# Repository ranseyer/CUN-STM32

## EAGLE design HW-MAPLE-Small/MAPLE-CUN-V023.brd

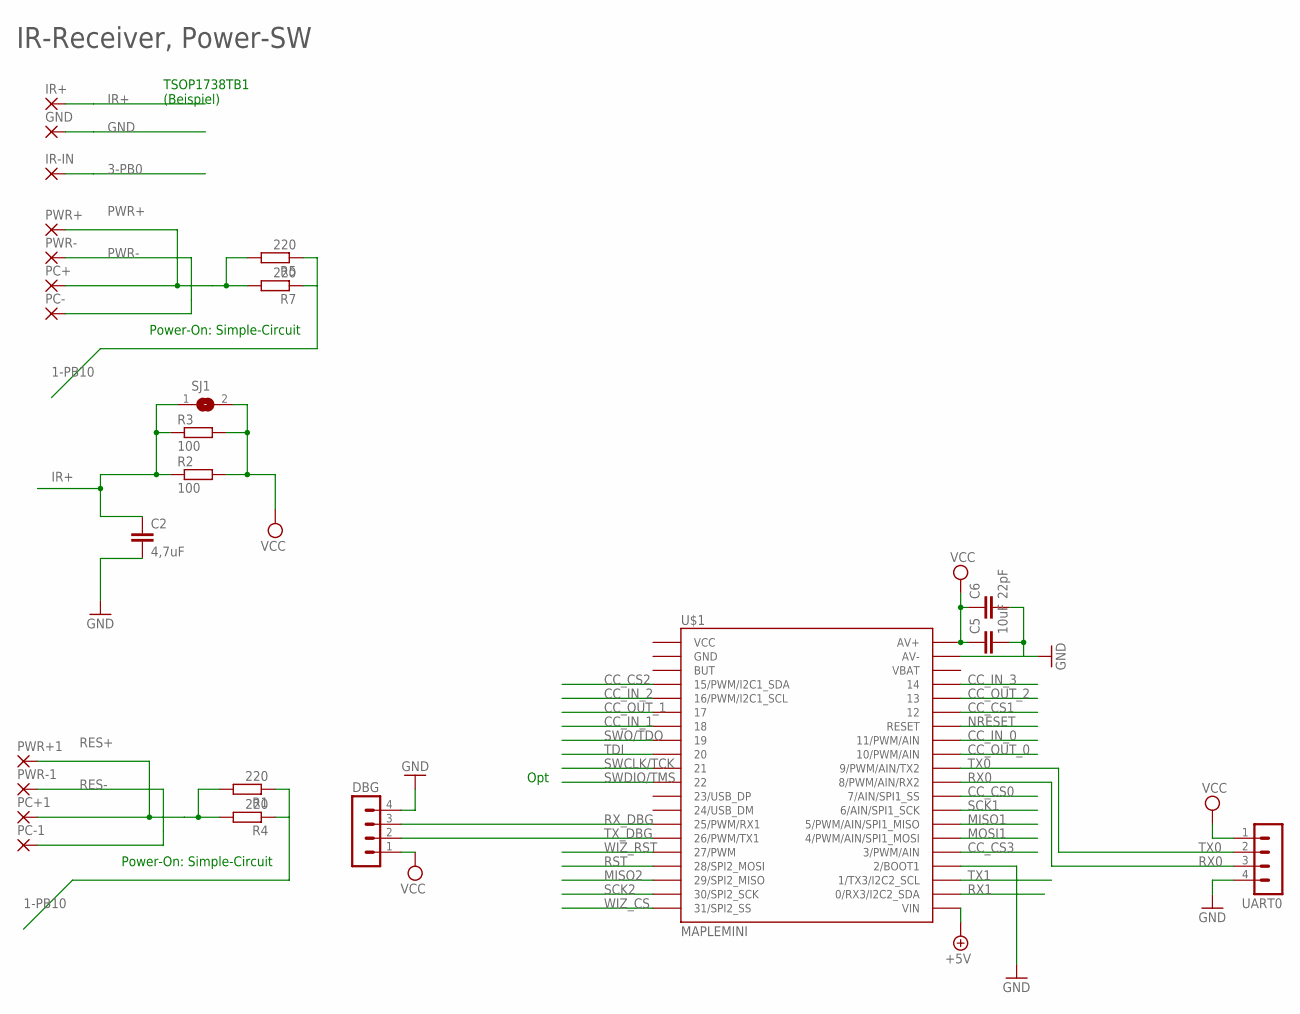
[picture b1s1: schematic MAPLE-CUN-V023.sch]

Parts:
C2: 4,7uF; C1206K
C5: 10uF; C1210
C6: 22pF; C0805
DBG: MA04-1
GND: SMD2; SMD1,27-2,54
IR+: SMD2; SMD1,27-2,54
IR-IN: SMD2; SMD1,27-2,54
PC+, PC+1: SMD2; SMD1,27-2,54
PC-, PC-1: SMD2; SMD1,27-2,54
PWR+, PWR+1: SMD2; SMD1,27-2,54
PWR-, PWR-1: SMD2; SMD1,27-2,54
R1, R5: 220; 0204/7
R2: 100; 0204/7
R3: 100; R0805W
R4, R7: 220; R0805W
SJ1: SJ
U$1: MAPLEMINI; 20-DIP
UART0: MA04-1

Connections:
1-PB10: R1.1, R4.1, R5.1, R7.1
3-PB0: IR-IN.1
+5V: U$1.21 (VIN)
CC_CS0: U$1.29 (7/AIN/SPI1_SS)
CC_CS1: U$1.35 (12)
CC_CS2: U$1.4 (15/PWM/I2C1_SDA)
CC_CS3: U$1.25 (3/PWM/AIN)
CC_IN_0: U$1.33 (11/PWM/AIN)
CC_IN_1: U$1.7 (18)
CC_IN_2: U$1.5 (16/PWM/I2C1_SCL)
CC_IN_3: U$1.37 (14)
CC_OUT_0: U$1.32 (10/PWM/AIN)
CC_OUT_1: U$1.6 (17)
CC_OUT_2: U$1.36 (13)
GND: C2.2, C5.2, C6.2, DBG.4, GND.1, U$1.24 (2/BOOT1), U$1.39 (AV-), UART0.4
IR+: C2.1, IR+.1, R2.1, R3.1, SJ1.1
MISO1: U$1.27 (5/PWM/AIN/SPI1_MISO)
MISO2: U$1.18 (29/SPI2_MISO)
MOSI1: U$1.26 (4/PWM/AIN/SPI1_MOSI)
NRESET: U$1.34 (RESET)
PWR+: PC+.1, PWR+.1, R5.2, R7.2
PWR-: PC-.1, PWR-.1
RES+: PC+1.1, PWR+1.1, R1.2, R4.2
RES-: PC-1.1, PWR-1.1
RST: U$1.17 (28/SPI2_MOSI)
RX0: U$1.30 (8/PWM/AIN/RX2), UART0.3
RX1: U$1.22 (0/RX3/I2C2_SDA)
RX_DBG: DBG.3, U$1.14 (25/PWM/RX1)
SCK1: U$1.28 (6/AIN/SPI1_SCK)
SCK2: U$1.19 (30/SPI2_SCK)
SWCLK/TCK: U$1.10 (21)
SWDIO/TMS: U$1.11 (22)
SWO/TDO: U$1.8 (19)
TDI: U$1.9 (20)
TX0: U$1.31 (9/PWM/AIN/TX2), UART0.2
TX1: U$1.23 (1/TX3/I2C2_SCL)
TX_DBG: DBG.2, U$1.15 (26/PWM/TX1)
VCC: C5.1, C6.1, DBG.1, R2.2, R3.2, SJ1.2, U$1.40 (AV+), UART0.1
WIZ_CS: U$1.20 (31/SPI2_SS)
WIZ_RST: U$1.16 (27/PWM)

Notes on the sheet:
Opt
TSOP1738TB1 (Beispiel)
Power-On: Simple-Circuit
IR-Receiver, Power-SW

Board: 2 copper layers, 24 parts (0 on the bottom side), 12 nets, no tracks yet.

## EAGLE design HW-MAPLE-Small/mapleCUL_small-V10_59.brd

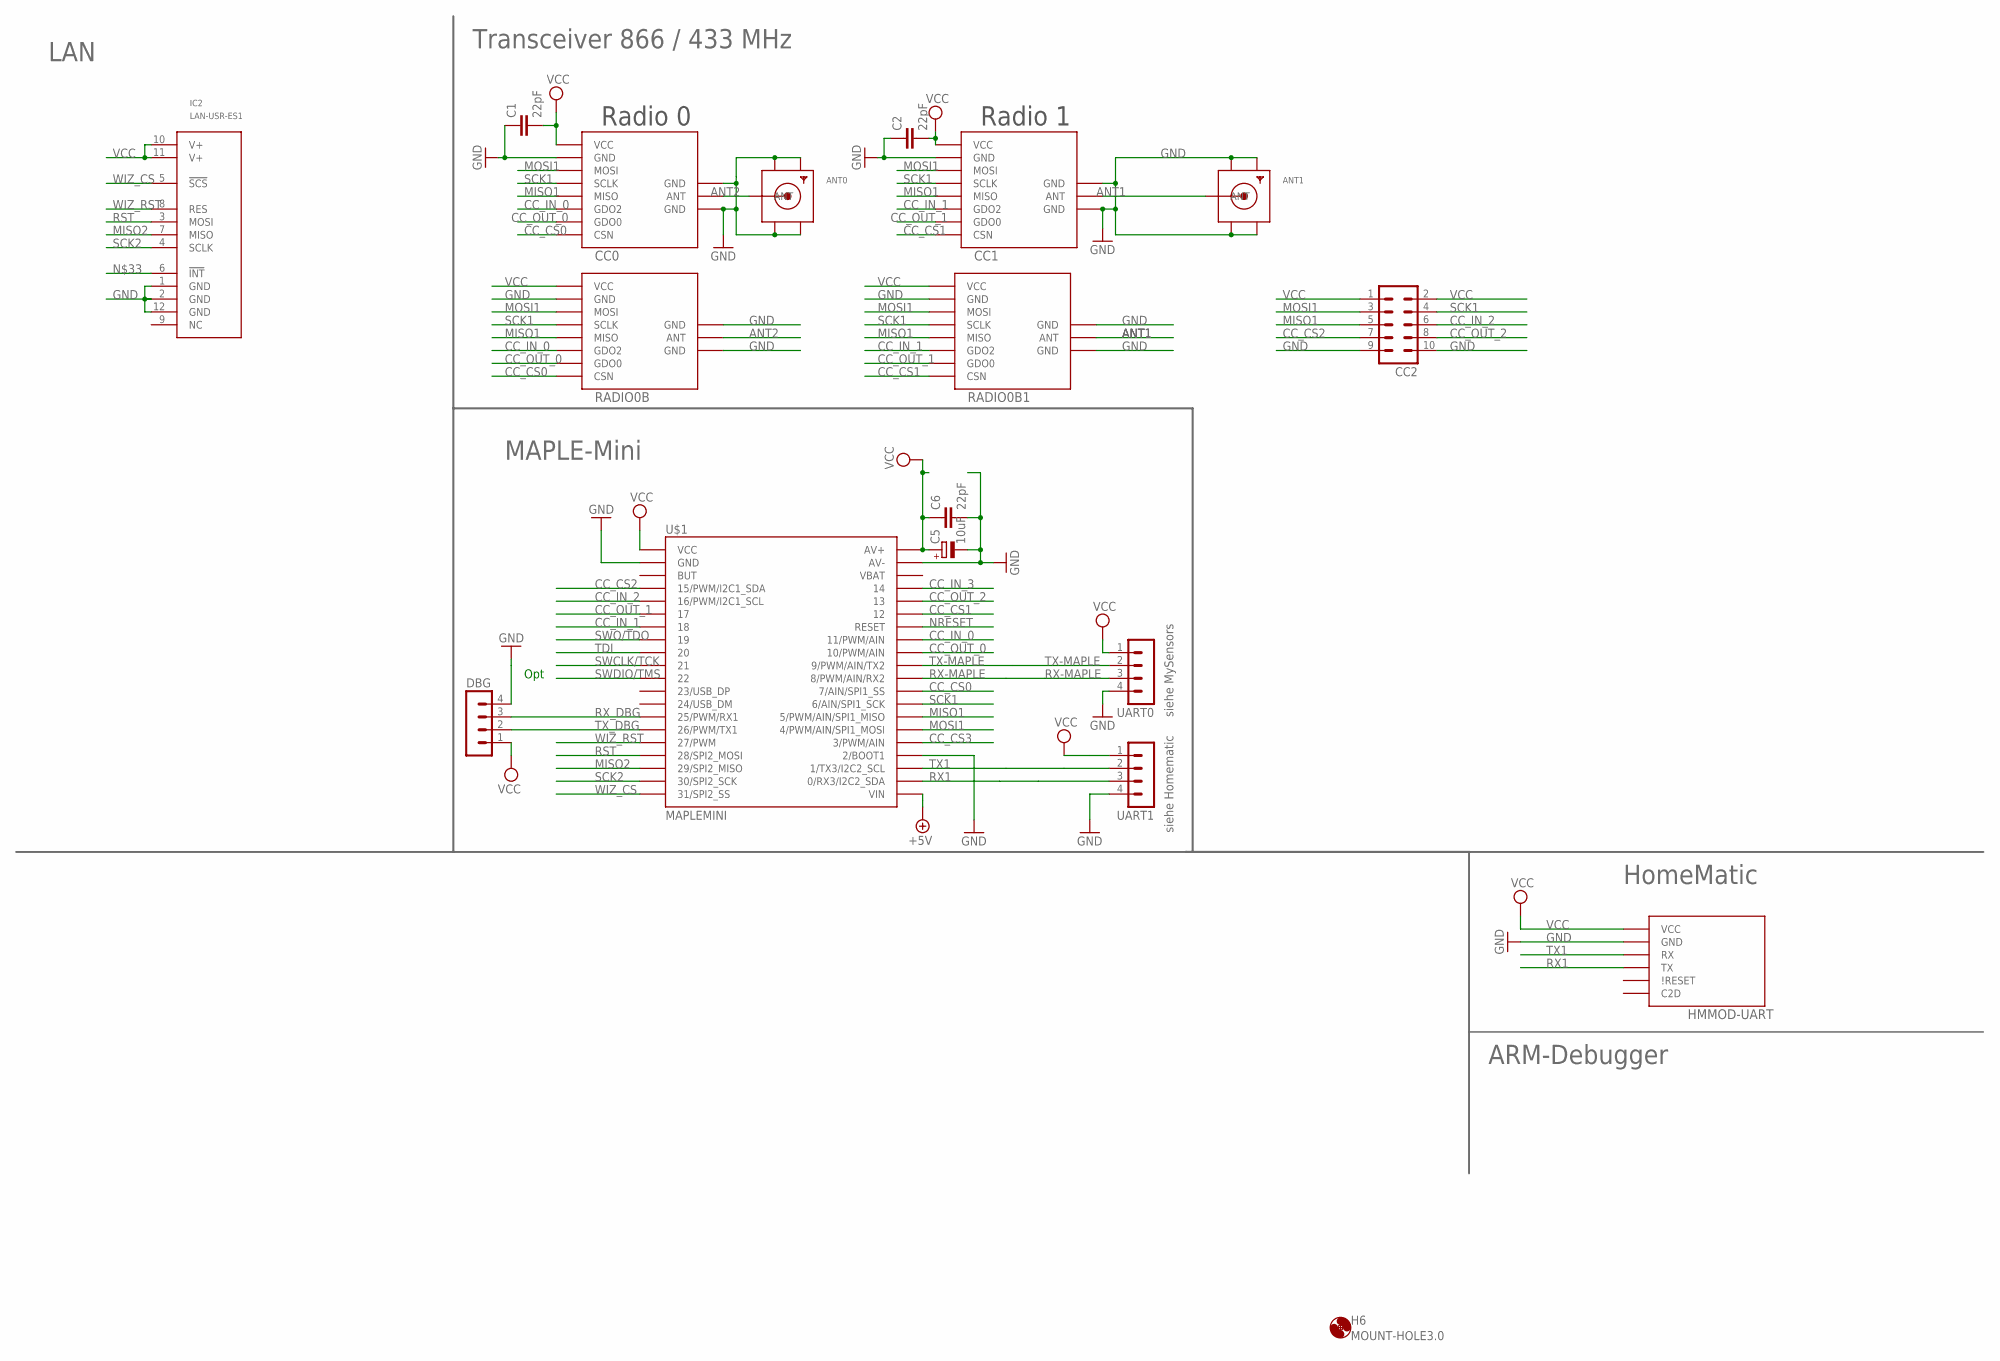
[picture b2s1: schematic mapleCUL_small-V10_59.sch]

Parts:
ANT0, ANT1: SMACONNECTOR_EDGE_UFL; SMA_EDGELAUNCH_UFL
C1, C2, C6: 22pF; C0805
C5: 10uF; R/2012-12W
CC0: CC1101; CC1101_MODULE1_SMD
CC1: CC1101_MODULE1SMD; CC1101_MODULE1_SMD
CC2: MA05-2
DBG: MA04-1
H6: MOUNT-HOLE3.0; 3,0
HMMOD-UART: HM-MOD-UARTDIL; HM-MOD-UART-DIL
IC2: LAN-USR-ES1; USR-ES1
RADIO0B: CC1101_MODULE1SMALL; CC1101_MODULE1_SMD
RADIO0B1: CC1101_MODULE1SMD; CC1101_MODULE1_SMD
U$1: MAPLEMINI; 20-DIP
UART0, UART1: MA04-1

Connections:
+5V: U$1.21 (VIN)
ANT1: ANT1.P (ANT), CC1.ANT, RADIO0B1.ANT
ANT2: ANT0.P (ANT), CC0.ANT, RADIO0B.ANT
CC_CS0: CC0.CSN, RADIO0B.CSN, U$1.29 (7/AIN/SPI1_SS)
CC_CS1: CC1.CSN, RADIO0B1.CSN, U$1.35 (12)
CC_CS2: CC2.7, U$1.4 (15/PWM/I2C1_SDA)
CC_CS3: U$1.25 (3/PWM/AIN)
CC_IN_0: CC0.GDO2, RADIO0B.GDO2, U$1.33 (11/PWM/AIN)
CC_IN_1: CC1.GDO2, RADIO0B1.GDO2, U$1.7 (18)
CC_IN_2: CC2.6, U$1.5 (16/PWM/I2C1_SCL)
CC_IN_3: U$1.37 (14)
CC_OUT_0: CC0.GDO0, RADIO0B.GDO0, U$1.32 (10/PWM/AIN)
CC_OUT_1: CC1.GDO0, RADIO0B1.GDO0, U$1.6 (17)
CC_OUT_2: CC2.8, U$1.36 (13)
GND: ANT0.GND@1 (GND1), ANT0.GND@2 (GND2), ANT0.GND@3 (GND3), ANT0.GND@4 (GND4), ANT1.GND@1 (GND1), ANT1.GND@2 (GND2), ANT1.GND@3 (GND3), ANT1.GND@4 (GND4), C1.1, C2.1, C5.-, C6.2, CC0.GND@0 (GND), CC0.GND@1 (GND), CC0.GND@2 (GND), CC1.GND@0 (GND), CC1.GND@1 (GND), CC1.GND@2 (GND), CC2.9, CC2.10, DBG.4, HMMOD-UART.2 (GND), IC2.1 (GND), IC2.2 (GND), IC2.12 (GND), RADIO0B.GND@0 (GND), RADIO0B.GND@1 (GND), RADIO0B.GND@2 (GND), RADIO0B1.GND@0 (GND), RADIO0B1.GND@1 (GND), RADIO0B1.GND@2 (GND), U$1.2 (GND), U$1.24 (2/BOOT1), U$1.39 (AV-), UART0.4, UART1.4
MISO1: CC0.MISO, CC1.MISO, CC2.5, RADIO0B.MISO, RADIO0B1.MISO, U$1.27 (5/PWM/AIN/SPI1_MISO)
MISO2: IC2.7 (MISO), U$1.18 (29/SPI2_MISO)
MOSI1: CC0.MOSI, CC1.MOSI, CC2.3, RADIO0B.MOSI, RADIO0B1.MOSI, U$1.26 (4/PWM/AIN/SPI1_MOSI)
NRESET: U$1.34 (RESET)
RST: IC2.3 (MOSI), U$1.17 (28/SPI2_MOSI)
RX1: HMMOD-UART.5 (TX), U$1.22 (0/RX3/I2C2_SDA), UART1.3
RX-MAPLE: U$1.30 (8/PWM/AIN/RX2), UART0.3
RX_DBG: DBG.3, U$1.14 (25/PWM/RX1)
SCK1: CC0.SCLK, CC1.SCLK, CC2.4, RADIO0B.SCLK, RADIO0B1.SCLK, U$1.28 (6/AIN/SPI1_SCK)
SCK2: IC2.4 (SCLK), U$1.19 (30/SPI2_SCK)
SWCLK/TCK: U$1.10 (21)
SWDIO/TMS: U$1.11 (22)
SWO/TDO: U$1.8 (19)
TDI: U$1.9 (20)
TX1: HMMOD-UART.6 (RX), U$1.23 (1/TX3/I2C2_SCL), UART1.2
TX-MAPLE: U$1.31 (9/PWM/AIN/TX2), UART0.2
TX_DBG: DBG.2, U$1.15 (26/PWM/TX1)
VCC: C1.2, C2.2, C5.+, C6.1, CC0.VCC, CC1.VCC, CC2.1, CC2.2, DBG.1, HMMOD-UART.1 (VCC), IC2.10 (V+), IC2.11 (V+), RADIO0B.VCC, RADIO0B1.VCC, U$1.1 (VCC), U$1.40 (AV+), UART0.1, UART1.1
WIZ_CS: IC2.5 (!SCS!), U$1.20 (31/SPI2_SS)
WIZ_RST: IC2.8 (RES), U$1.16 (27/PWM)

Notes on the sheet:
Radio 1
Radio 0
Opt
siehe Homematic
siehe MySensors
HomeMatic
MAPLE-Mini
Transceiver 866 / 433 MHz
LAN
ARM-Debugger

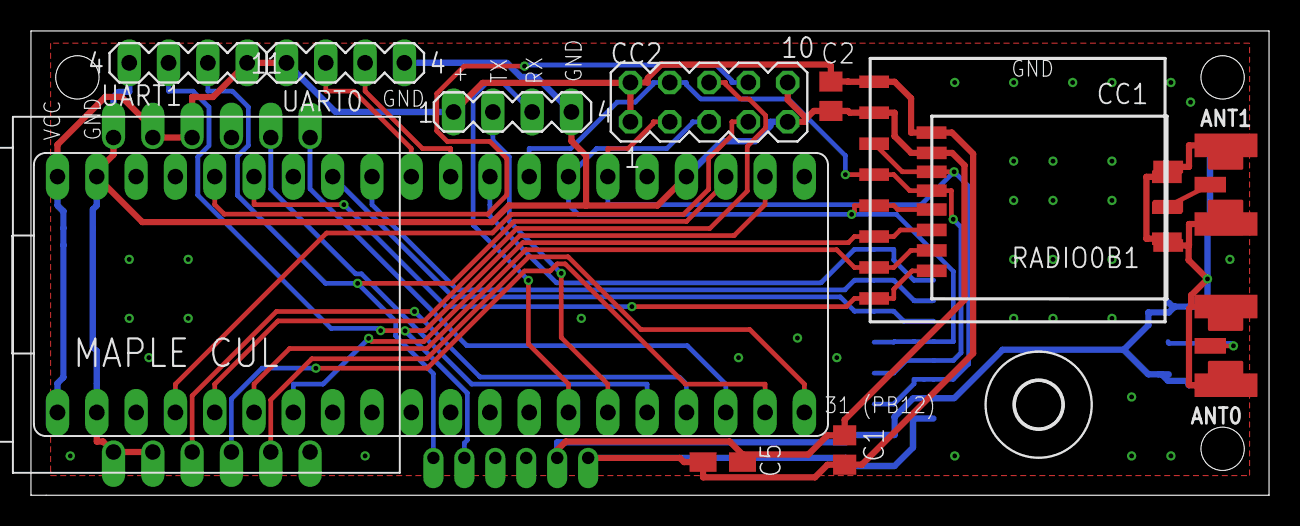
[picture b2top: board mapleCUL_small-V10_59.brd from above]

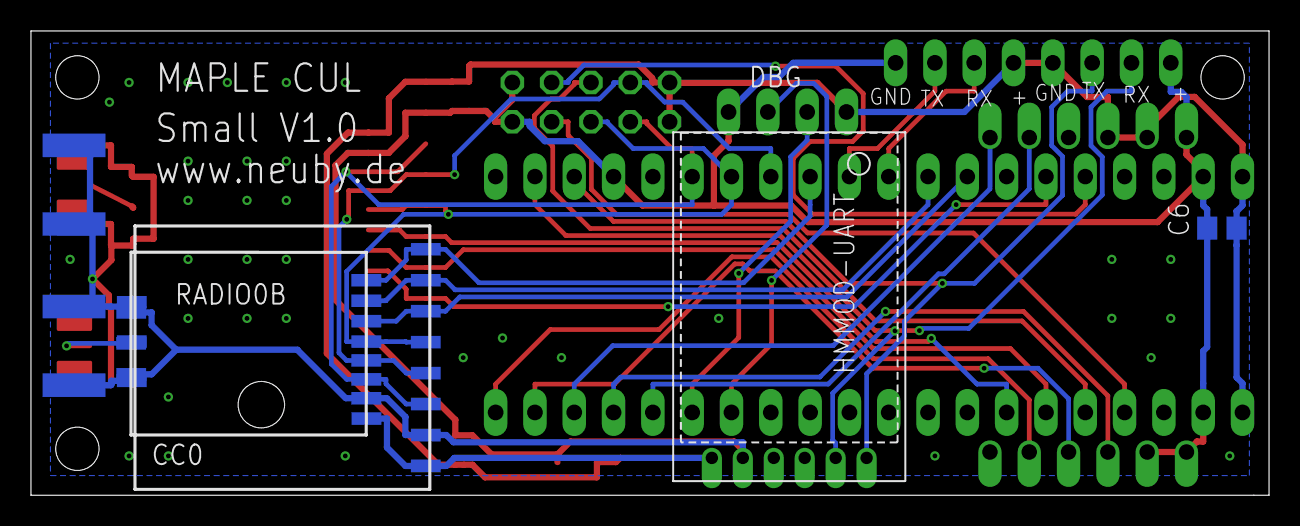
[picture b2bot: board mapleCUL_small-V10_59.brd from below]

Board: 2 copper layers, 80.0 x 30.0 mm, 18 parts (4 on the bottom side), 27 nets.

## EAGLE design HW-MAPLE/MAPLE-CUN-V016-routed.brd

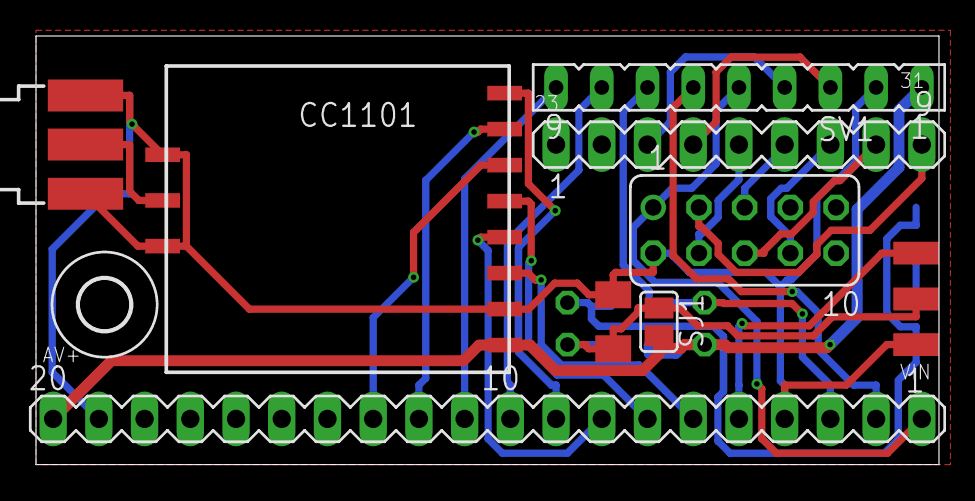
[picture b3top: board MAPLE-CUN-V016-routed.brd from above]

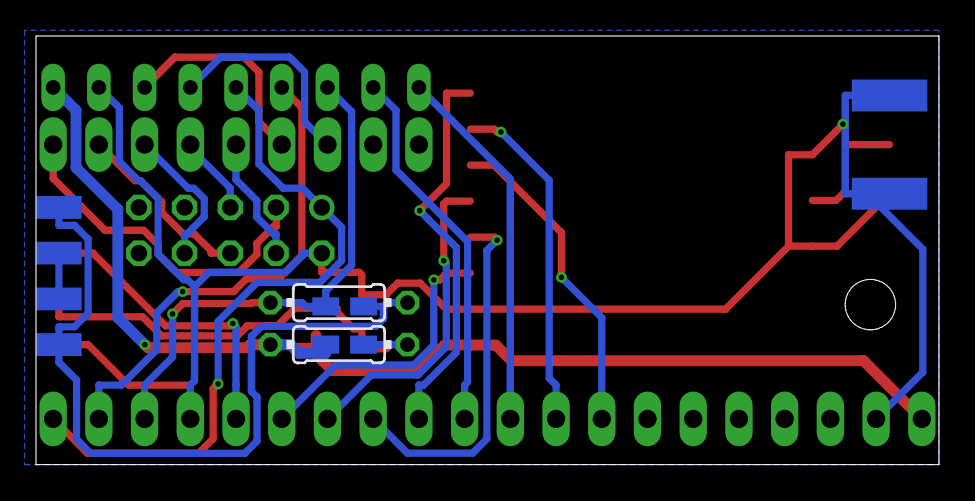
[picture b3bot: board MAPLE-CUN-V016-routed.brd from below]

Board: 2 copper layers, 50.2 x 23.8 mm, 20 parts (8 on the bottom side), 25 nets.

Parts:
C2: 4,7uF; C1206K
CC1101: CC1101_MODULE1SMD; CC1101_MODULE1_SMD
GND: SMD1,27-2,54
H1: MOUNT-HOLE2.8; 2,8
IR+: SMD1,27-2,54
IR-IN: SMD1,27-2,54
PC+: SMD1,27-2,54
PC-: SMD1,27-2,54
PWR+: SMD1,27-2,54
PWR-: SMD1,27-2,54
R2: 100; 0204/7
R3: 100; R0805W
R5: 220; 0204/7
R7: 220; R0805W
SJ1: SJ
SV1: FE09
SV4: MA20-1
SV5: MA09-1
W5100: FE05-2
X1: SMA

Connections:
0-PB11: SV1.6, SV4.2
1-PB10: R5.1, R7.1, SV1.7, SV4.3
3-PB0: IR-IN.1, SV4.5
+5V: SV1.5, SV4.1, W5100.1
CC_IN_0: CC1101.GDO2, SV4.13
CC_OUT_0: CC1101.GDO0, SV4.12
CSN: CC1101.CSN, SV4.9
GND: C2.2, CC1101.GND@0, CC1101.GND@1, CC1101.GND@2, GND.1, SV1.2, SV4.4, SV4.19, W5100.2, X1.GND@1, X1.GND@2, X1.GND@3, X1.GND@4
IR+: C2.1, IR+.1, R2.1, R3.1, SJ1.1
MISO2: SV5.7, W5100.8
MOSI: CC1101.MOSI, SV4.6
MOSI2: SV5.6, W5100.5
unnamed: CC1101.ANT, X1.1
unnamed: CC1101.MISO, SV4.7
unnamed: CC1101.SCLK, SV4.8
PWR+: PC+.1, PWR+.1, R5.2, R7.2
PWR-: PC-.1, PWR-.1
RX1: SV1.4, SV5.3
S2RX: SV1.8, SV4.10
S2TX: SV1.9, SV4.11
SCK2: SV5.8, W5100.6
TX1: SV1.3, SV5.4
VCC: CC1101.VCC, R2.2, R3.2, SJ1.2, SV1.1, SV4.20
WIZ_CS: SV5.9, W5100.3
WIZ_RST: SV5.5, W5100.4

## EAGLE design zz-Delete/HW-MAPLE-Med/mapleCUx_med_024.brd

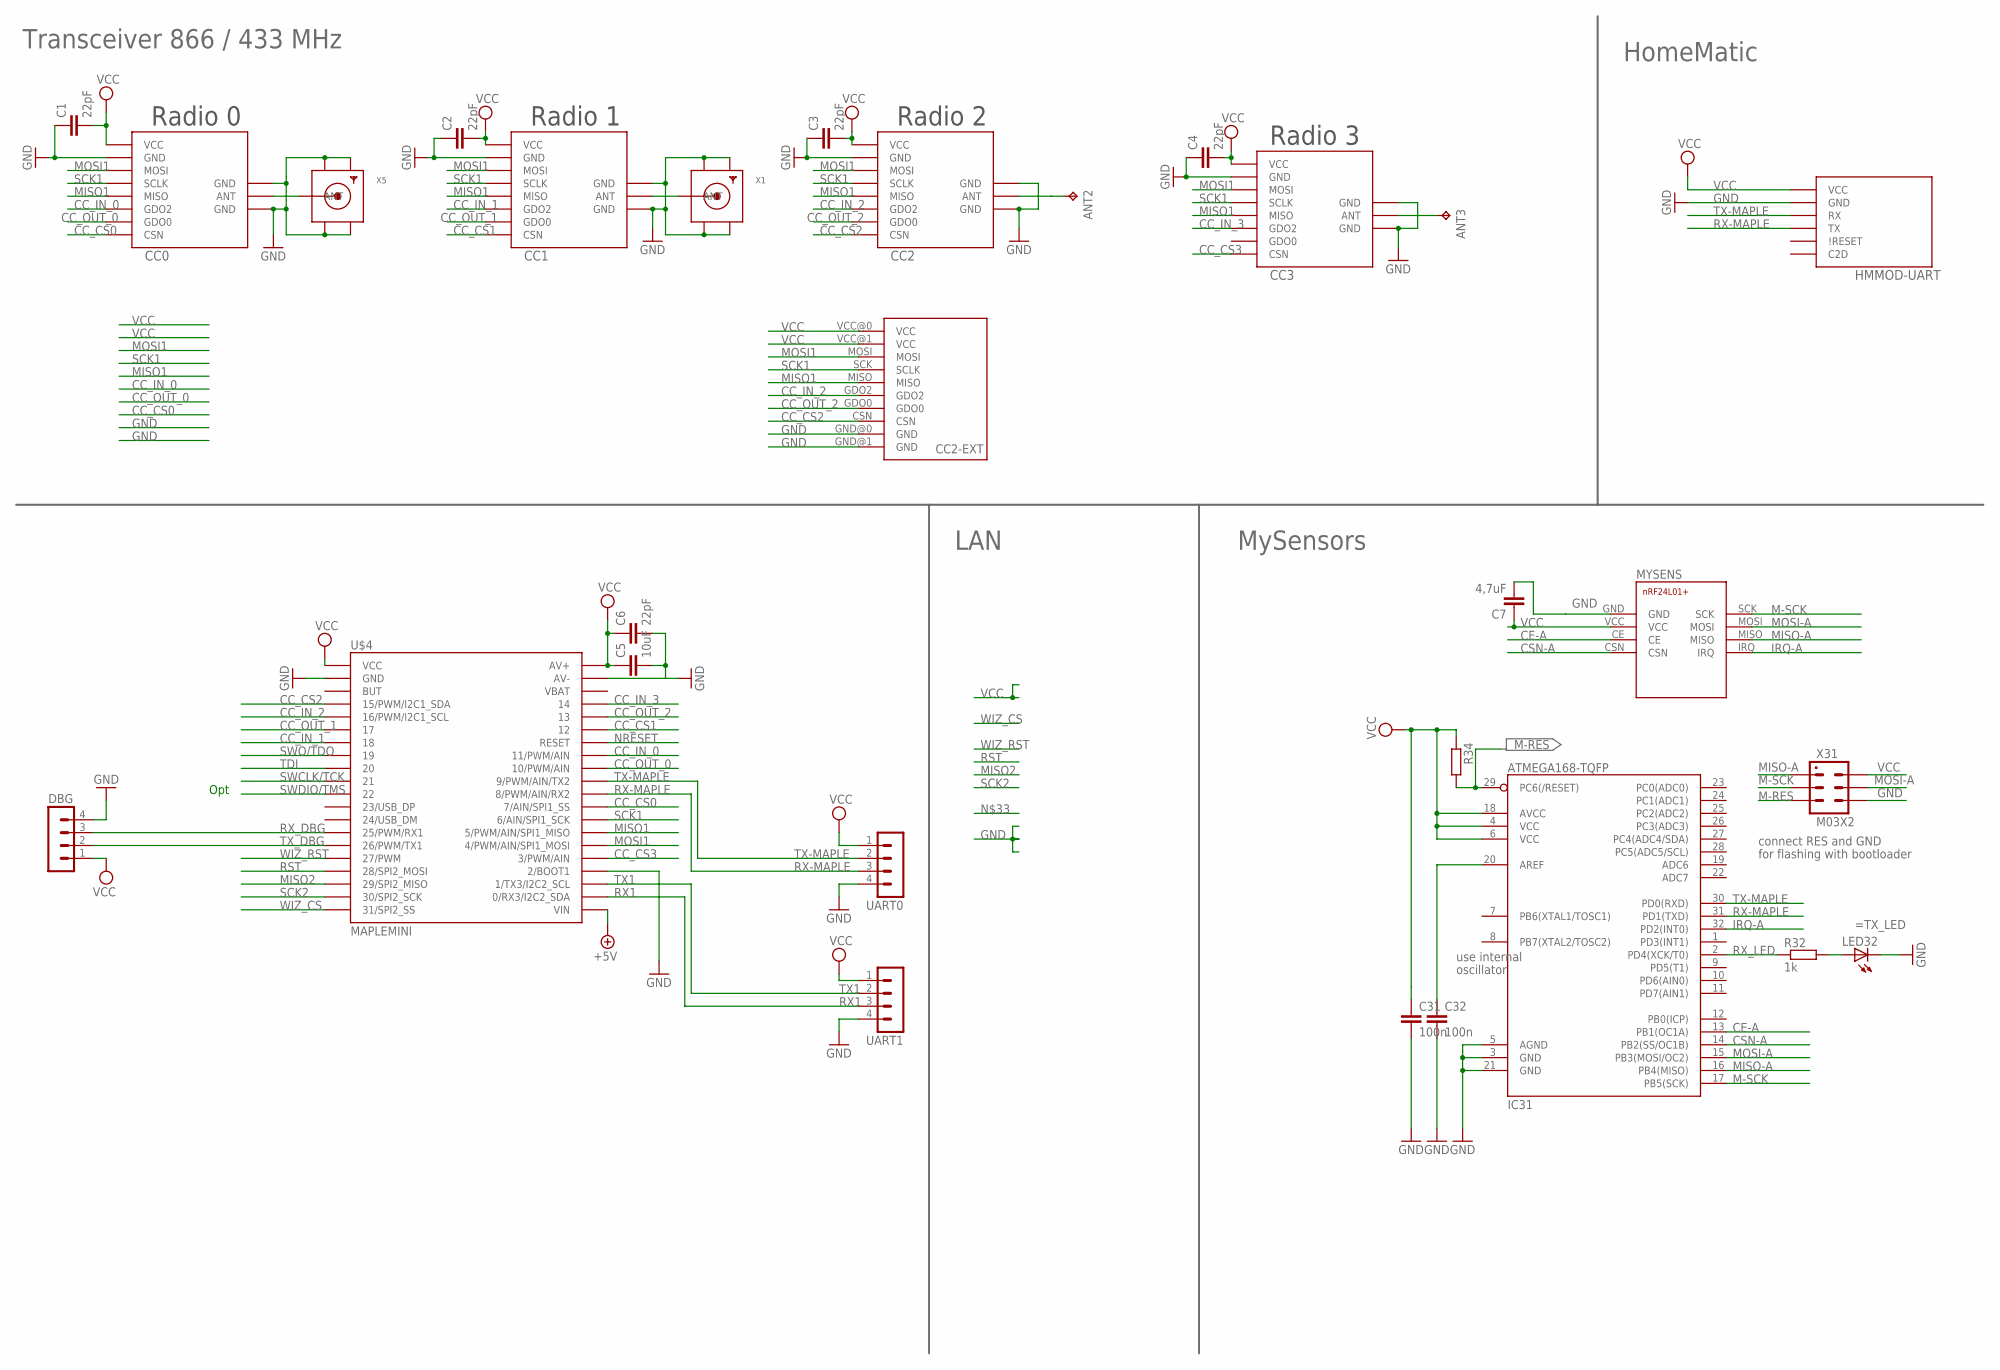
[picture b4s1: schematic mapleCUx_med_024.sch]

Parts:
ANT2, ANT3: TPPAD1-13; P1-13
C1, C2, C3, C4, C6: 22pF; C0805
C5: 10uF; C1210
C7: 4,7uF; C1210
C31, C32: 100n; C0805
CC0: CC1101; CC1101_MODULE1_SMD
CC1, CC2, CC3: CC1101_MODULE1SMD; CC1101_MODULE1_SMD
CC2-EXT: CC1101_MODULE3_DIL
DBG: MA04-1
HMMOD-UART: HM-MOD-UARTDIL; HM-MOD-UART-DIL
IC31: ATMEGA168-TQFP; TQFP32-08
LED32: LEDCHIPLED_0805; CHIPLED_0805
MYSENS: NRF24L01+SMD
R32: 1k; R0805
R34: R-EU_R0805; R0805
U$4: MAPLEMINI; 20-DIP
UART0, UART1: MA04-1
X1, X5: SMACONNECTOR_EDGE_UFL; SMA_EDGELAUNCH_UFL
X31: M03X2; 2X03-1.27MM_SMD

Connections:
+5V: U$4.21 (VIN)
CC_CS0: CC0.CSN, U$4.29 (7/AIN/SPI1_SS)
CC_CS1: CC1.CSN, U$4.35 (12)
CC_CS2: CC2.CSN, CC2-EXT.CSN, U$4.4 (15/PWM/I2C1_SDA)
CC_CS3: CC3.CSN, U$4.25 (3/PWM/AIN)
CC_IN_0: CC0.GDO2, U$4.33 (11/PWM/AIN)
CC_IN_1: CC1.GDO2, U$4.7 (18)
CC_IN_2: CC2.GDO2, CC2-EXT.GDO2, U$4.5 (16/PWM/I2C1_SCL)
CC_IN_3: CC3.GDO2, U$4.37 (14)
CC_OUT_0: CC0.GDO0, U$4.32 (10/PWM/AIN)
CC_OUT_1: CC1.GDO0, U$4.6 (17)
CC_OUT_2: CC2.GDO0, CC2-EXT.GDO0, U$4.36 (13)
CE-A: IC31.13 (PB1(OC1A)), MYSENS.CE
CSN-A: IC31.14 (PB2(SS/OC1B)), MYSENS.CSN
GND: C1.1, C2.1, C3.1, C4.1, C5.2, C6.2, C7.2, C31.2, C32.2, CC0.GND@0 (GND), CC0.GND@1 (GND), CC0.GND@2 (GND), CC1.GND@0 (GND), CC1.GND@1 (GND), CC1.GND@2 (GND), CC2.GND@0 (GND), CC2.GND@1 (GND), CC2.GND@2 (GND), CC2-EXT.GND@0 (GND), CC2-EXT.GND@1 (GND), CC3.GND@0 (GND), CC3.GND@1 (GND), CC3.GND@2 (GND), DBG.4, HMMOD-UART.2 (GND), IC31.3 (GND), IC31.5 (AGND), IC31.21 (GND), LED32.C, MYSENS.GND, U$4.2 (GND), U$4.24 (2/BOOT1), U$4.39 (AV-), UART0.4, UART1.4, X1.GND@1 (GND1), X1.GND@2 (GND2), X1.GND@3 (GND3), X1.GND@4 (GND4), X5.GND@1 (GND1), X5.GND@2 (GND2), X5.GND@3 (GND3), X5.GND@4 (GND4), X31.P$6 (6)
IRQ-A: IC31.32 (PD2(INT0)), MYSENS.IRQ
M-RES: IC31.29 (PC6(/RESET)), R34.2, X31.P$5 (5)
M-SCK: IC31.17 (PB5(SCK)), MYSENS.SCK, X31.P$3 (3)
MISO1: CC0.MISO, CC1.MISO, CC2.MISO, CC2-EXT.MISO, CC3.MISO, U$4.27 (5/PWM/AIN/SPI1_MISO)
MISO2: U$4.18 (29/SPI2_MISO)
MISO-A: IC31.16 (PB4(MISO)), MYSENS.MISO, X31.P$1 (1)
MOSI1: CC0.MOSI, CC1.MOSI, CC2.MOSI, CC2-EXT.MOSI, CC3.MOSI, U$4.26 (4/PWM/AIN/SPI1_MOSI)
MOSI-A: IC31.15 (PB3(MOSI/OC2)), MYSENS.MOSI, X31.P$4 (4)
unnamed: CC1.ANT, X1.P (ANT)
unnamed: ANT3.TP, CC3.ANT
unnamed: ANT2.TP, CC2.ANT
unnamed: CC0.ANT, X5.P (ANT)
unnamed: LED32.A, R32.2
unnamed: C32.1, IC31.20 (AREF)
NRESET: U$4.34 (RESET)
RST: U$4.17 (28/SPI2_MOSI)
RX1: U$4.22 (0/RX3/I2C2_SDA), UART1.3
RX-MAPLE: HMMOD-UART.5 (TX), IC31.31 (PD1(TXD)), U$4.30 (8/PWM/AIN/RX2), UART0.3
RX_DBG: DBG.3, U$4.14 (25/PWM/RX1)
RX_LED: IC31.2 (PD4(XCK/T0)), R32.1
SCK1: CC0.SCLK, CC1.SCLK, CC2.SCLK, CC2-EXT.SCK (SCLK), CC3.SCLK, U$4.28 (6/AIN/SPI1_SCK)
SCK2: U$4.19 (30/SPI2_SCK)
SWCLK/TCK: U$4.10 (21)
SWDIO/TMS: U$4.11 (22)
SWO/TDO: U$4.8 (19)
TDI: U$4.9 (20)
TX1: U$4.23 (1/TX3/I2C2_SCL), UART1.2
TX-MAPLE: HMMOD-UART.6 (RX), IC31.30 (PD0(RXD)), U$4.31 (9/PWM/AIN/TX2), UART0.2
TX_DBG: DBG.2, U$4.15 (26/PWM/TX1)
VCC: C1.2, C2.2, C3.2, C4.2, C5.1, C6.1, C7.1, C31.1, CC0.VCC, CC1.VCC, CC2.VCC, CC2-EXT.VCC@0 (VCC), CC2-EXT.VCC@1 (VCC), CC3.VCC, DBG.1, HMMOD-UART.1 (VCC), IC31.4 (VCC), IC31.6 (VCC), IC31.18 (AVCC), MYSENS.VCC, R34.1, U$4.1 (VCC), U$4.40 (AV+), UART0.1, UART1.1, X31.P$2 (2)
WIZ_CS: U$4.20 (31/SPI2_SS)
WIZ_RST: U$4.16 (27/PWM)

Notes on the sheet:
Opt
use internal
oscillator
=TX_LED
connect RES and GND
for flashing with bootloader
Radio 1
Radio 0
Radio 2
Radio 3
Transceiver 866 / 433 MHz
LAN
HomeMatic
MySensors

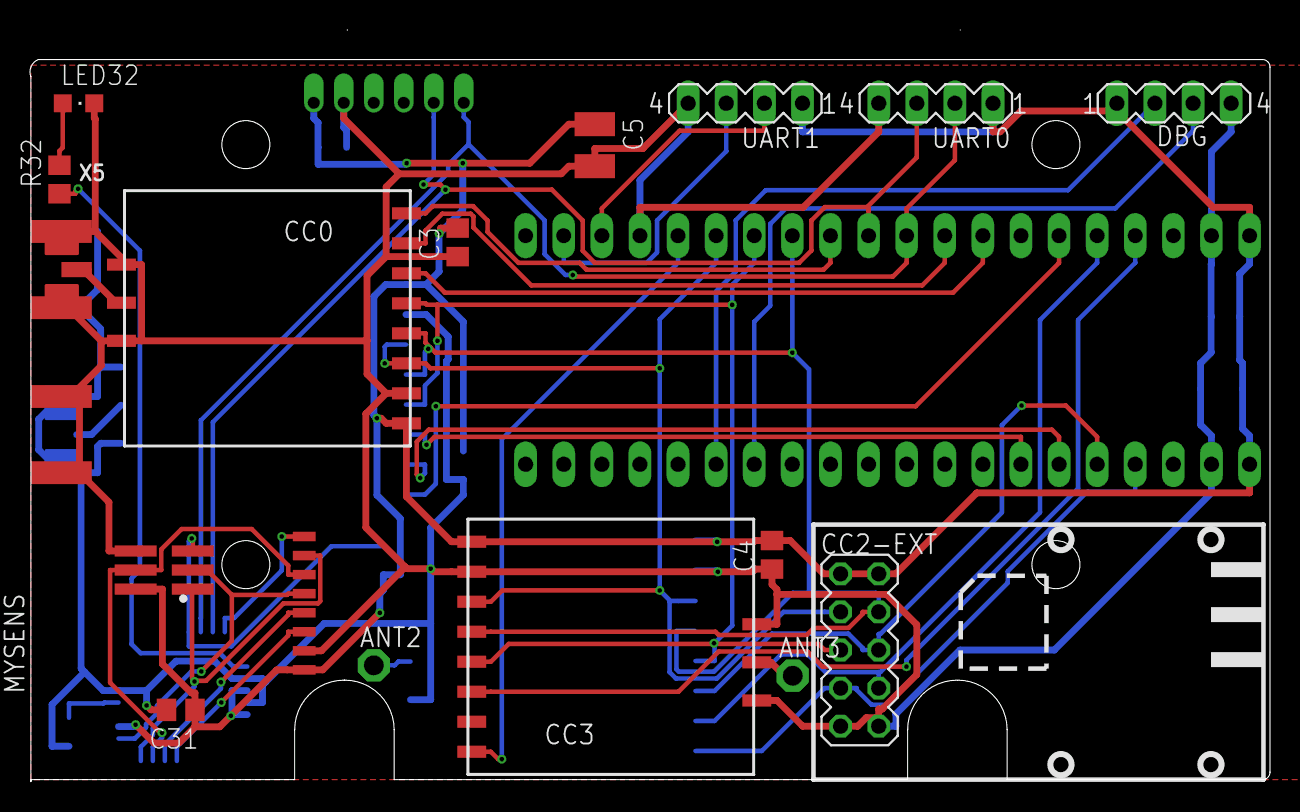
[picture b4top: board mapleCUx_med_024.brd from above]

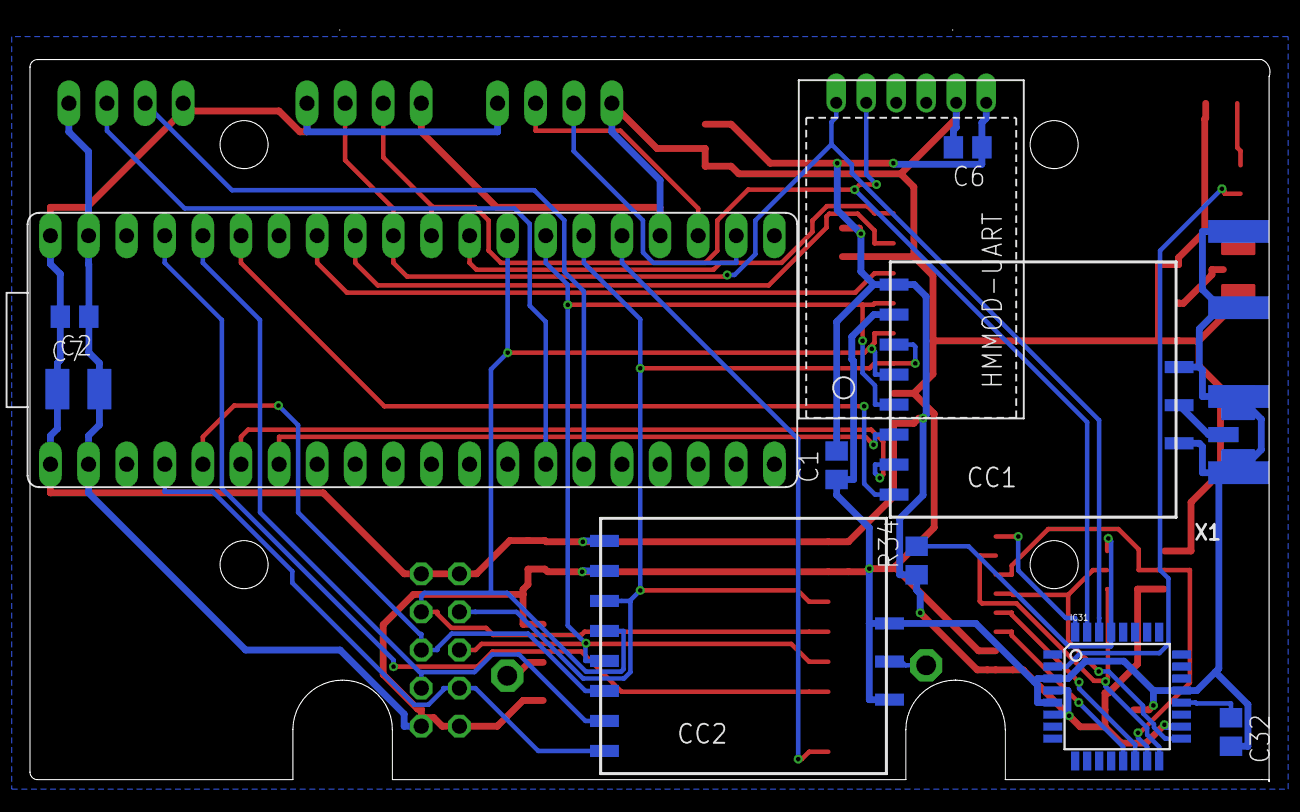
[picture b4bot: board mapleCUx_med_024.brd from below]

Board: 2 copper layers, 82.7 x 50.1 mm, 29 parts (12 on the bottom side), 36 nets.
